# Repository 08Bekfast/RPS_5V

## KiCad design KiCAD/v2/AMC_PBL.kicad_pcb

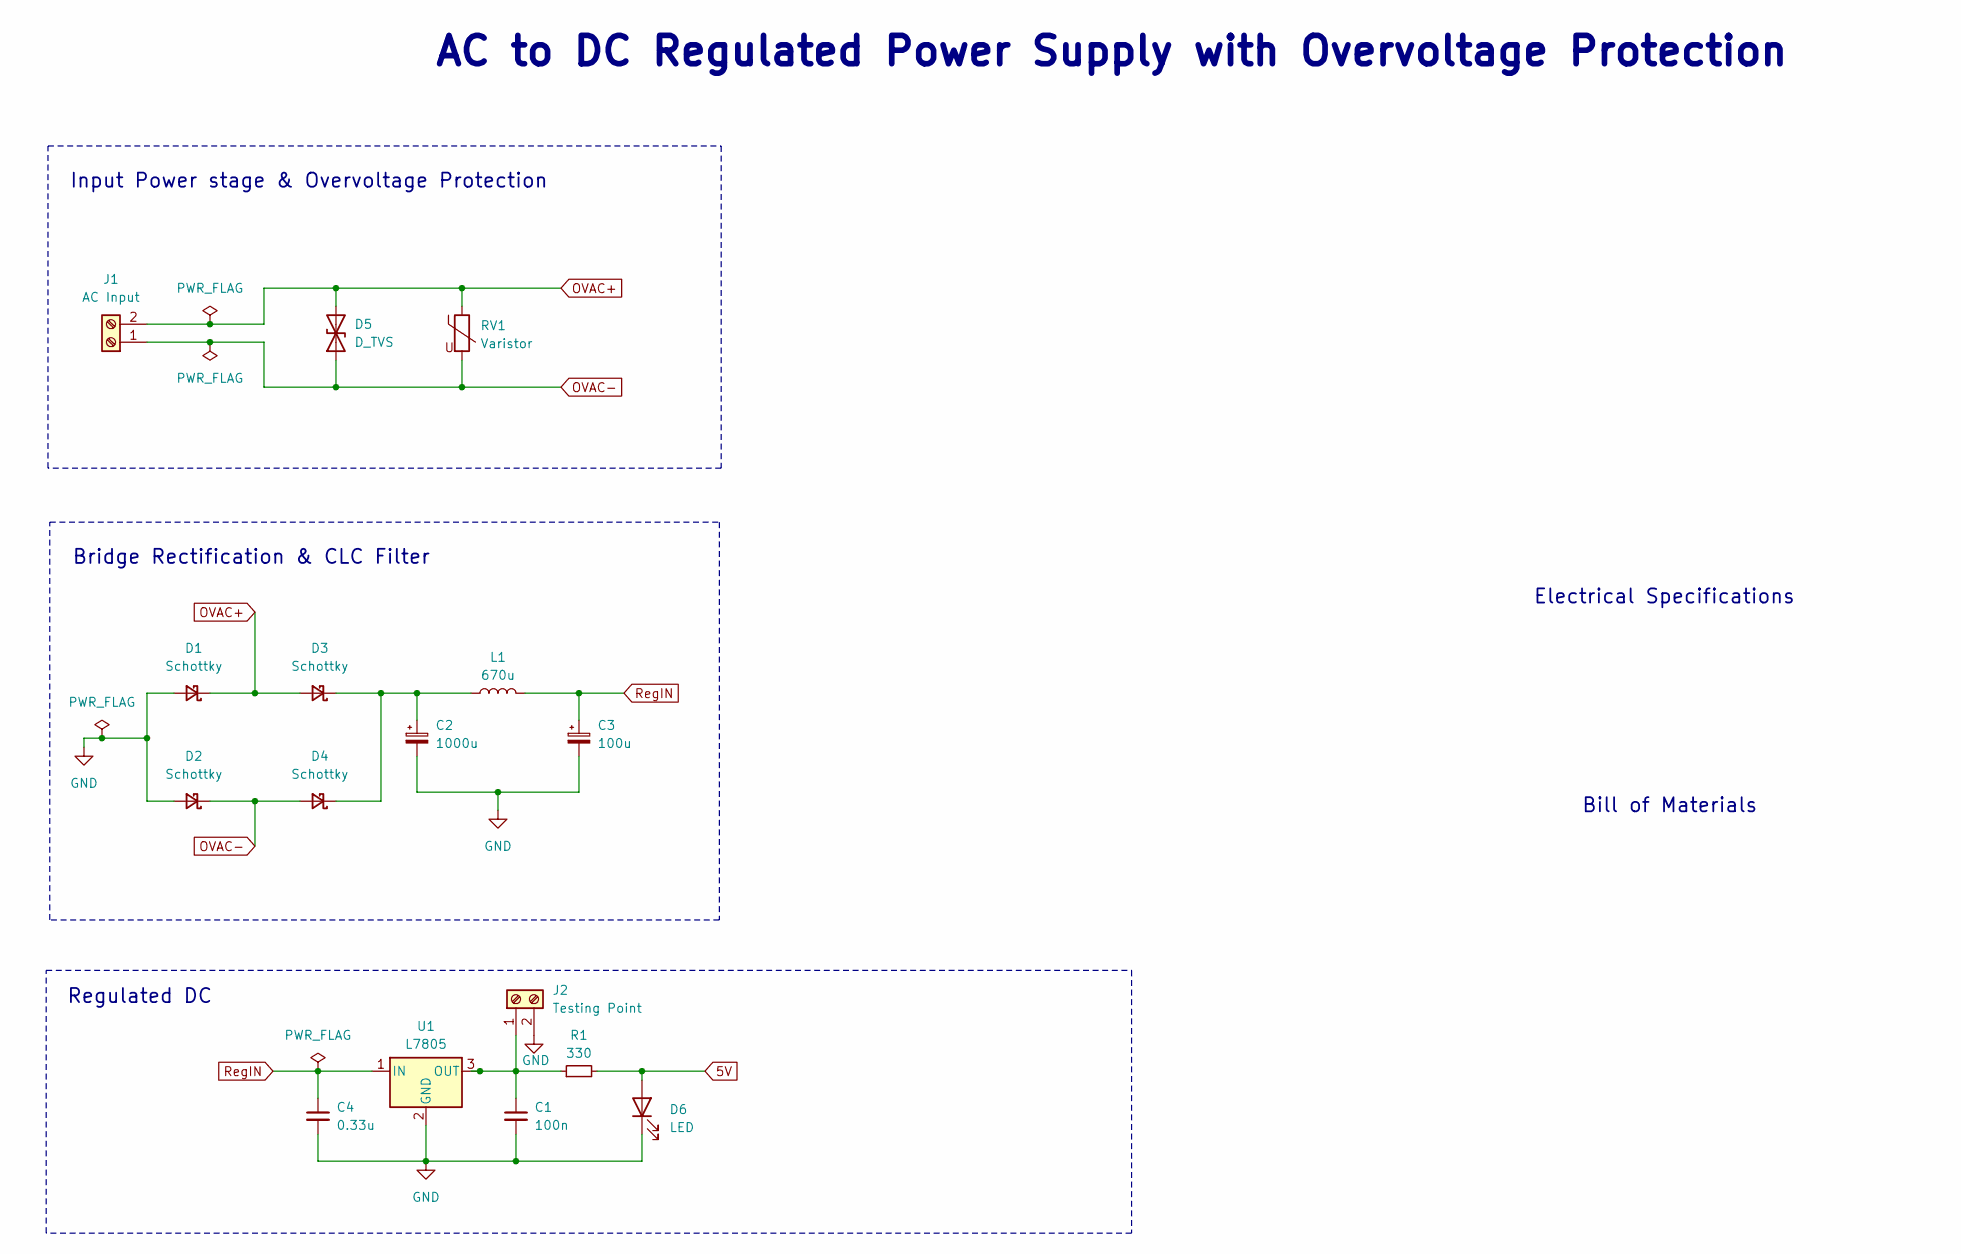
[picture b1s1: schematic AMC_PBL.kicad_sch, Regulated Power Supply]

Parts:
C1: 100n; C_Disc_D5.0mm_W2.5mm_P2.50mm
C2: 1000u; CP_Radial_D10.0mm_P2.50mm
C3: 100u; CP_Radial_D6.3mm_P2.50mm
C4: 0.33u; C_Disc_D5.0mm_W2.5mm_P2.50mm
D1, D2, D3, D4: Schottky; D_DO-41_SOD81_P10.16mm_Horizontal
D5: D_TVS; D_DO-15_P10.16mm_Horizontal
D6: LED; LED_D5.0mm
J1: AC Input; TerminalBlock_MaiXu_MX126-5.0-02P_1x02_P5.00mm
J2: Testing Point; PinHeader_1x02_P2.54mm_Vertical
L1: 670u; L_Radial_D10.0mm_P5.00mm_Fastron_07M
R1: 330; R_Axial_DIN0207_L6.3mm_D2.5mm_P7.62mm_Horizontal
RV1: Varistor; RV_Disc_D12mm_W4.2mm_P7.5mm
U1: L7805; TO-220-3_Vertical

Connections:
5V: D6.2 (A), R1.2
GND: C1.2, C2.2, C3.2, C4.2, D1.2 (A), D2.2 (A), D6.1 (K), J2.2, U1.2 (GND)
unnamed: C2.1, D3.1 (K), D4.1 (K), L1.1
unnamed: C1.1, J2.1, R1.1, U1.3 (OUT)
OVAC+: D1.1 (K), D3.2 (A), D5.2 (A2), J1.2, RV1.1
OVAC-: D2.1 (K), D4.2 (A), D5.1 (A1), J1.1, RV1.2
RegIN: C3.1, C4.1, L1.2, U1.1 (IN)

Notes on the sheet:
Bridge Rectification & CLC Filter
AC to DC Regulated Power Supply with Overvoltage Protection
Input Power stage & Overvoltage Protection
Bill of Materials
Electrical Specifications
Regulated DC

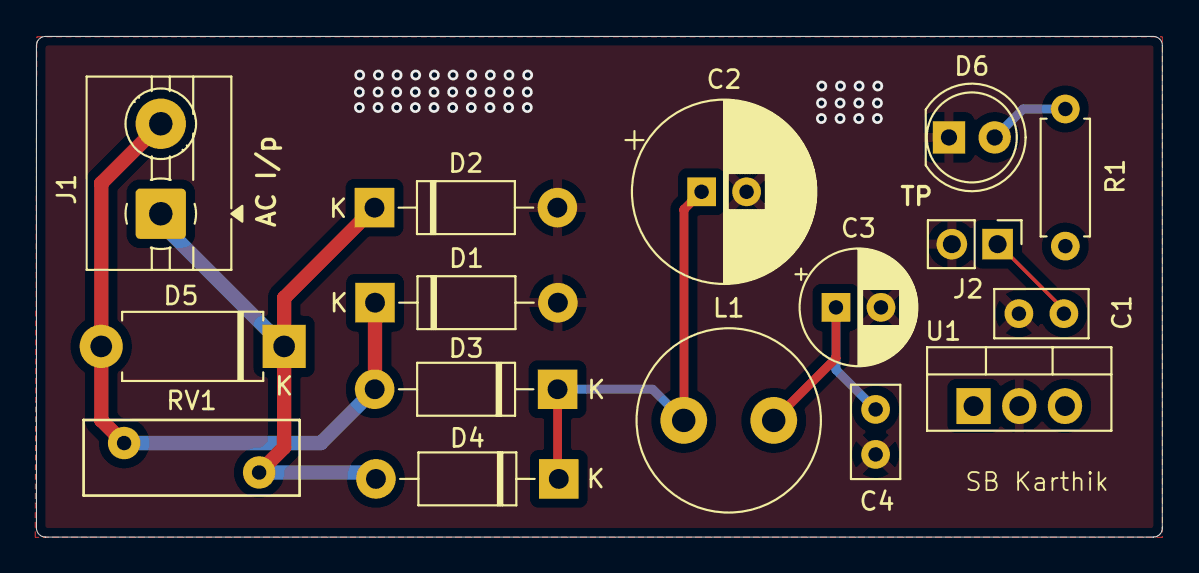
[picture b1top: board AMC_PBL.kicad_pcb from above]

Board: 2 copper layers, 62.5 x 27.8 mm, 16 parts (0 on the bottom side), 7 nets.

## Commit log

2026-06-15 Create KiCAD
2026-06-15 Create PCB
2026-06-15 Create changelog
2026-06-15 Create ,
2026-06-15 Create 1
2026-06-15 Create 2
2026-06-15 Add files via upload
    Added gnd stitching vias, cleaned up LDO routing & changed trace width to 0.8mm
2026-06-15 Create thing
2026-06-15 Add files via upload
    Original PCB
